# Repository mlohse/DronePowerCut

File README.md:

# DronePowerCut

This board is supposed to be connected between the main battery and the flight controller of a drone/opto-copter and provides an emergency power-off in case the drone get's out of control.
The board has been designed for 6s LiPo batteries (22.2V) and can handle continuous currents of up to 80A.

# Bill of Material (BOM)
The PCB can be ordered at OSH Park (they ship worldwide):

* https://oshpark.com/shared_projects/SKaDHxAu (rev.A)

It doesn't really matter of which brand/type you order resistors and capacitors, nor does this board require any tight tolerances. You can purchase whatever your local hardware dealer has on stock fitting the value/package described by the schematic.
However, for convenience I've created a virtual shopping basket at Reichelt Elektronik:

* https://www.reichelt.de/my/2021258

MosFETs and Voltage regulator are available at Farnell:

* https://de.farnell.com/infineon/auirfs8409-7trl/mosfet-n-kanal-40v-240a-to-263/dp/2839427?st=auirfs8409
* https://de.farnell.com/microchip/mic5219-3-6ym5-tr/ldo-0-5vdo-0-5a-3-6v-1-5sot23/dp/2510256?st=mic5219

# Building and Flashing the Firmware
You need to have an AVR toolchain installed (make, gcc, binutils)

On Arch Linux simply install the following packages:

`# pacman -S community/avr-gcc community/avr-binutils community/avr-libc`

You may likely want to install avrdude (of course if your programmer requires a different software you can skip this step):

`# pacman -S avrdude`

Please don't forget to adapt the `PROGRAMMER`/`PORT` section in the `Makefile` according to your programmer.

To build the firmware change into the `src` directory and run:

`# make`

...then connect the board to your ISP programmer - the boards needs to be powered (consumes < 50mA) through the programmer - and flash the firmware:

`# make program`

**Optional**: It shouldn't be necessary to flash fuses, as they are left to defaults. But in case the MCU behaves weird in any way...

`# make fuses`

Done.

# LED States (Debugging)

## Power LED (blue)
This led should always be flashing with 1Hz during opartion. If constantly lid or off the MCU has crashed - should never happen of course ;)

## Activity LED (green)
This led indicated whether there is a signal from the receiver:

* **off**: no signal
* **flashing with 5Hz**: invalid signal (pulse to short/long, see `CTRL_DECODER_VAL_MIN`/`CTRL_DECODER_VAL_MAX`)
* **constantly lid**: signal ok (during normal operation this should always be the case)

## OFF LED (red)
This led indicates when lid that power has been cut (emergency off active).

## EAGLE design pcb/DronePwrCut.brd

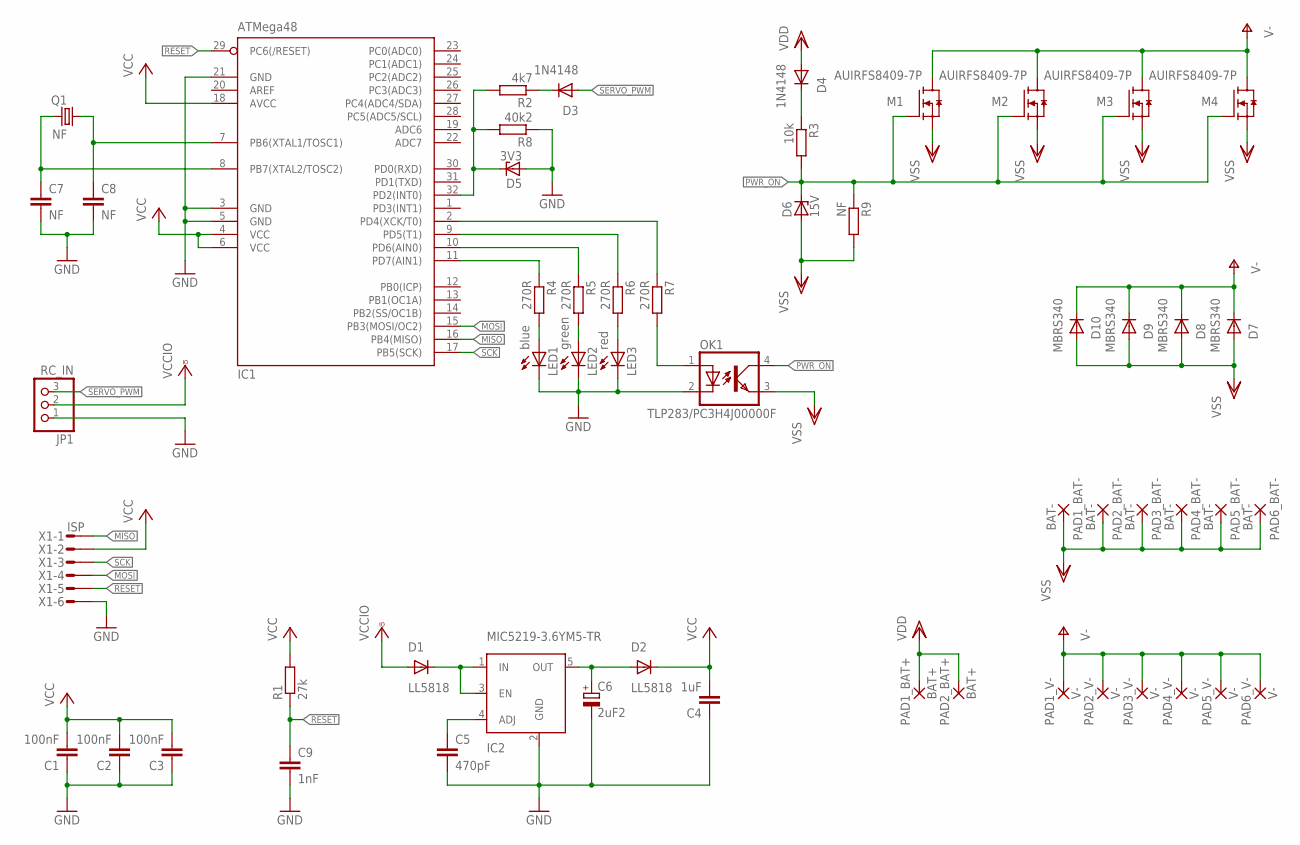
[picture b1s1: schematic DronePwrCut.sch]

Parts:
C1, C2, C3: 100nF; C1206K
C4: 1uF; C1206K
C5: 470pF; C1206K
C6: 2uF2; SMC_B
C7, C8: NF; C1206K
C9: 1nF; C1206K
D1, D2: LL5818; MELF-MLL41
D3, D4: 1N4148; SOD80C
D5: 3V3; SOD80C
D6: 15V; SOD80C
D7, D8, D9, D10: MBRS340; SMC
IC1: ATMega48; TQFP32-08
IC2: MIC5219-3.6YM5-TR; SOT23-5
JP1: RC_IN; 1X03
LED1: blue; CHIPLED_1206
LED2: green; CHIPLED_1206
LED3: red; CHIPLED_1206
M1, M2, M3, M4: AUIRFS8409-7P; P-TO263-7-1
OK1: TLP283/PC3H4J00000F; MINI-FLAT-4
PAD1_BAT+, PAD2_BAT+: BAT+; 1,6/0,8
PAD1_BAT-, PAD2_BAT-, PAD3_BAT-, PAD4_BAT-, PAD5_BAT-, PAD6_BAT-: BAT-; 1,6/0,8
PAD1_V-, PAD2_V-, PAD3_V-, PAD4_V-, PAD5_V-, PAD6_V-: V-; 1,6/0,8
Q1: NF; HC49UP
R1: 27k; R1206
R2: 4k7; R1206
R3: 10k; R1206
R4, R5, R6, R7: 270R; R1206
R8: 40k2; R1206
R9: NF; R1206
X1: ISP; MICROMATCH-6

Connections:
GND: C1.1, C2.1, C3.1, C4.1, C5.2, C6.-, C7.2, C8.2, C9.2, D5.A, IC1.3 (GND), IC1.5 (GND), IC1.21 (GND), IC2.2 (GND), JP1.1, LED1.C, LED2.C, LED3.C, OK1.2 (C), R8.1, X1.6
MISO: IC1.16 (PB4(MISO)), X1.1
MOSI: IC1.15 (PB3(MOSI/OC2)), X1.4
unnamed: C8.1, IC1.7 (PB6(XTAL1/TOSC1)), Q1.1
unnamed: C6.+, D2.A, IC2.5 (OUT)
unnamed: C5.1, IC2.4 (ADJ)
unnamed: D1.C, IC2.1 (IN), IC2.3 (EN)
unnamed: C7.1, IC1.8 (PB7(XTAL2/TOSC2)), Q1.2
unnamed: D5.C, IC1.32 (PD2(INT0)), R2.2, R8.2
unnamed: D3.C, R2.1
unnamed: D4.C, R3.1
unnamed: IC1.11 (PD7(AIN1)), R4.1
unnamed: IC1.10 (PD6(AIN0)), R5.1
unnamed: IC1.9 (PD5(T1)), R6.1
unnamed: IC1.2 (PD4(XCK/T0)), R7.1
unnamed: LED1.A, R4.2
unnamed: LED2.A, R5.2
unnamed: LED3.A, R6.2
unnamed: OK1.1 (A), R7.2
PWR_ON: D6.C, M1.1 (G), M2.1 (G), M3.1 (G), M4.1 (G), OK1.4 (COL), R3.2, R9.1
RESET: C9.1, IC1.29 (PC6(/RESET)), R1.1, X1.5
SCK: IC1.17 (PB5(SCK)), X1.3
SERVO_PWM: D3.A, JP1.3
V-: D7.C, D8.C, D9.C, D10.C, M1.7 (D), M2.7 (D), M3.7 (D), M4.7 (D), PAD1_V-.1, PAD2_V-.1, PAD3_V-.1, PAD4_V-.1, PAD5_V-.1, PAD6_V-.1
VCC: C1.2, C2.2, C3.2, C4.2, D2.C, IC1.4 (VCC), IC1.6 (VCC), IC1.18 (AVCC), R1.2, X1.2
VCCIO: D1.A, JP1.2
VDD: D4.A, PAD1_BAT+.1, PAD2_BAT+.1
VSS: D6.A, D7.A, D8.A, D9.A, D10.A, M1.2 (S), M1.3 (S), M1.4 (S), M1.5 (S), M1.6 (S), M2.2 (S), M2.3 (S), M2.4 (S), M2.5 (S), M2.6 (S), M3.2 (S), M3.3 (S), M3.4 (S), M3.5 (S), M3.6 (S), M4.2 (S), M4.3 (S), M4.4 (S), M4.5 (S), M4.6 (S), OK1.3 (EMIT), PAD1_BAT-.1, PAD2_BAT-.1, PAD3_BAT-.1, PAD4_BAT-.1, PAD5_BAT-.1, PAD6_BAT-.1, R9.2

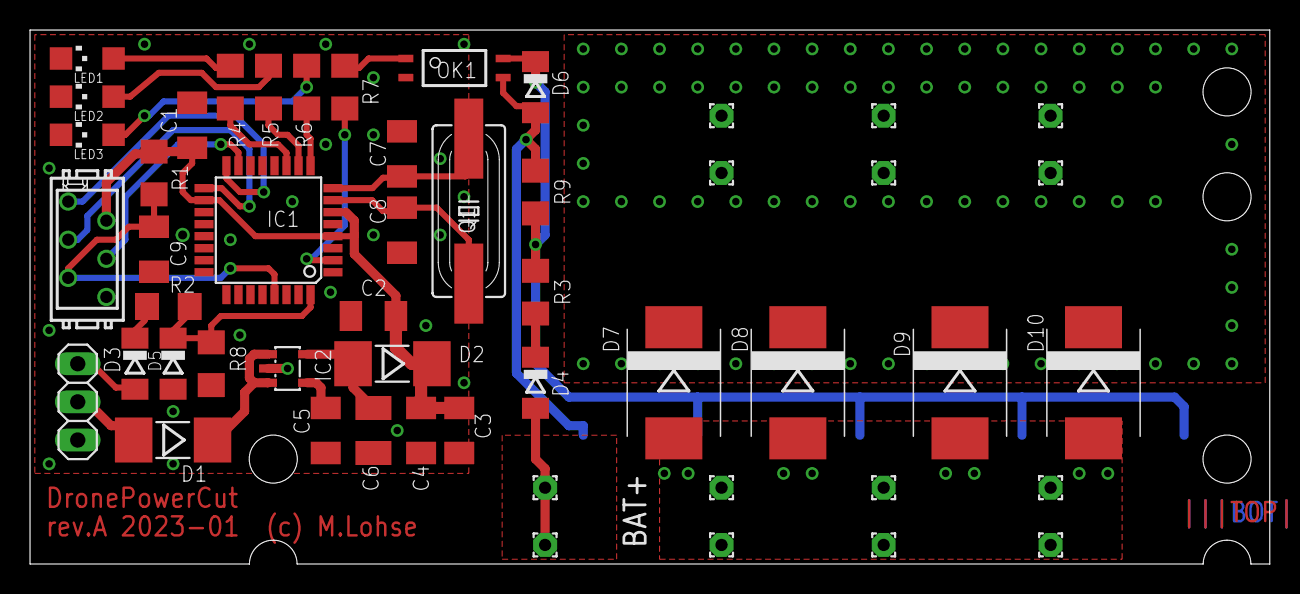
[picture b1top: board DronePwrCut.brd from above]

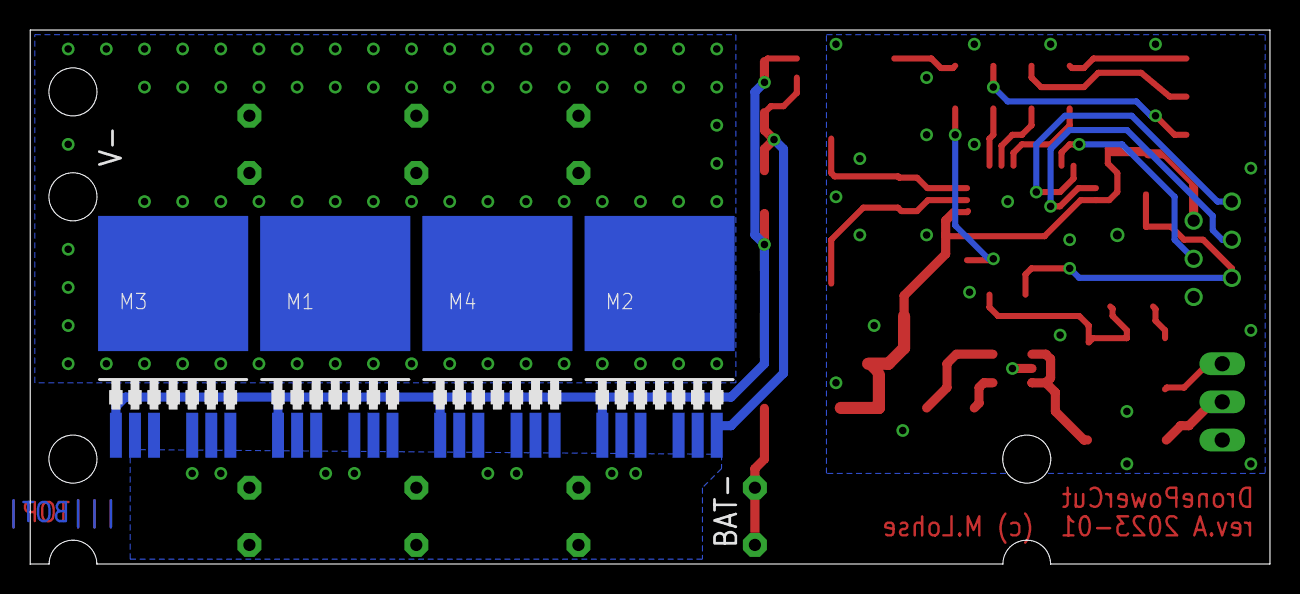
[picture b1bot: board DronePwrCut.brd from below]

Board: 2 copper layers, 82.5 x 35.5 mm, 55 parts (4 on the bottom side), 28 nets.

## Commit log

2023-02-25 initial version
2023-02-25 add section led states
2023-03-09 Change resistor values (R2, R8) to handle low voltage (3V3) input signals correctly
